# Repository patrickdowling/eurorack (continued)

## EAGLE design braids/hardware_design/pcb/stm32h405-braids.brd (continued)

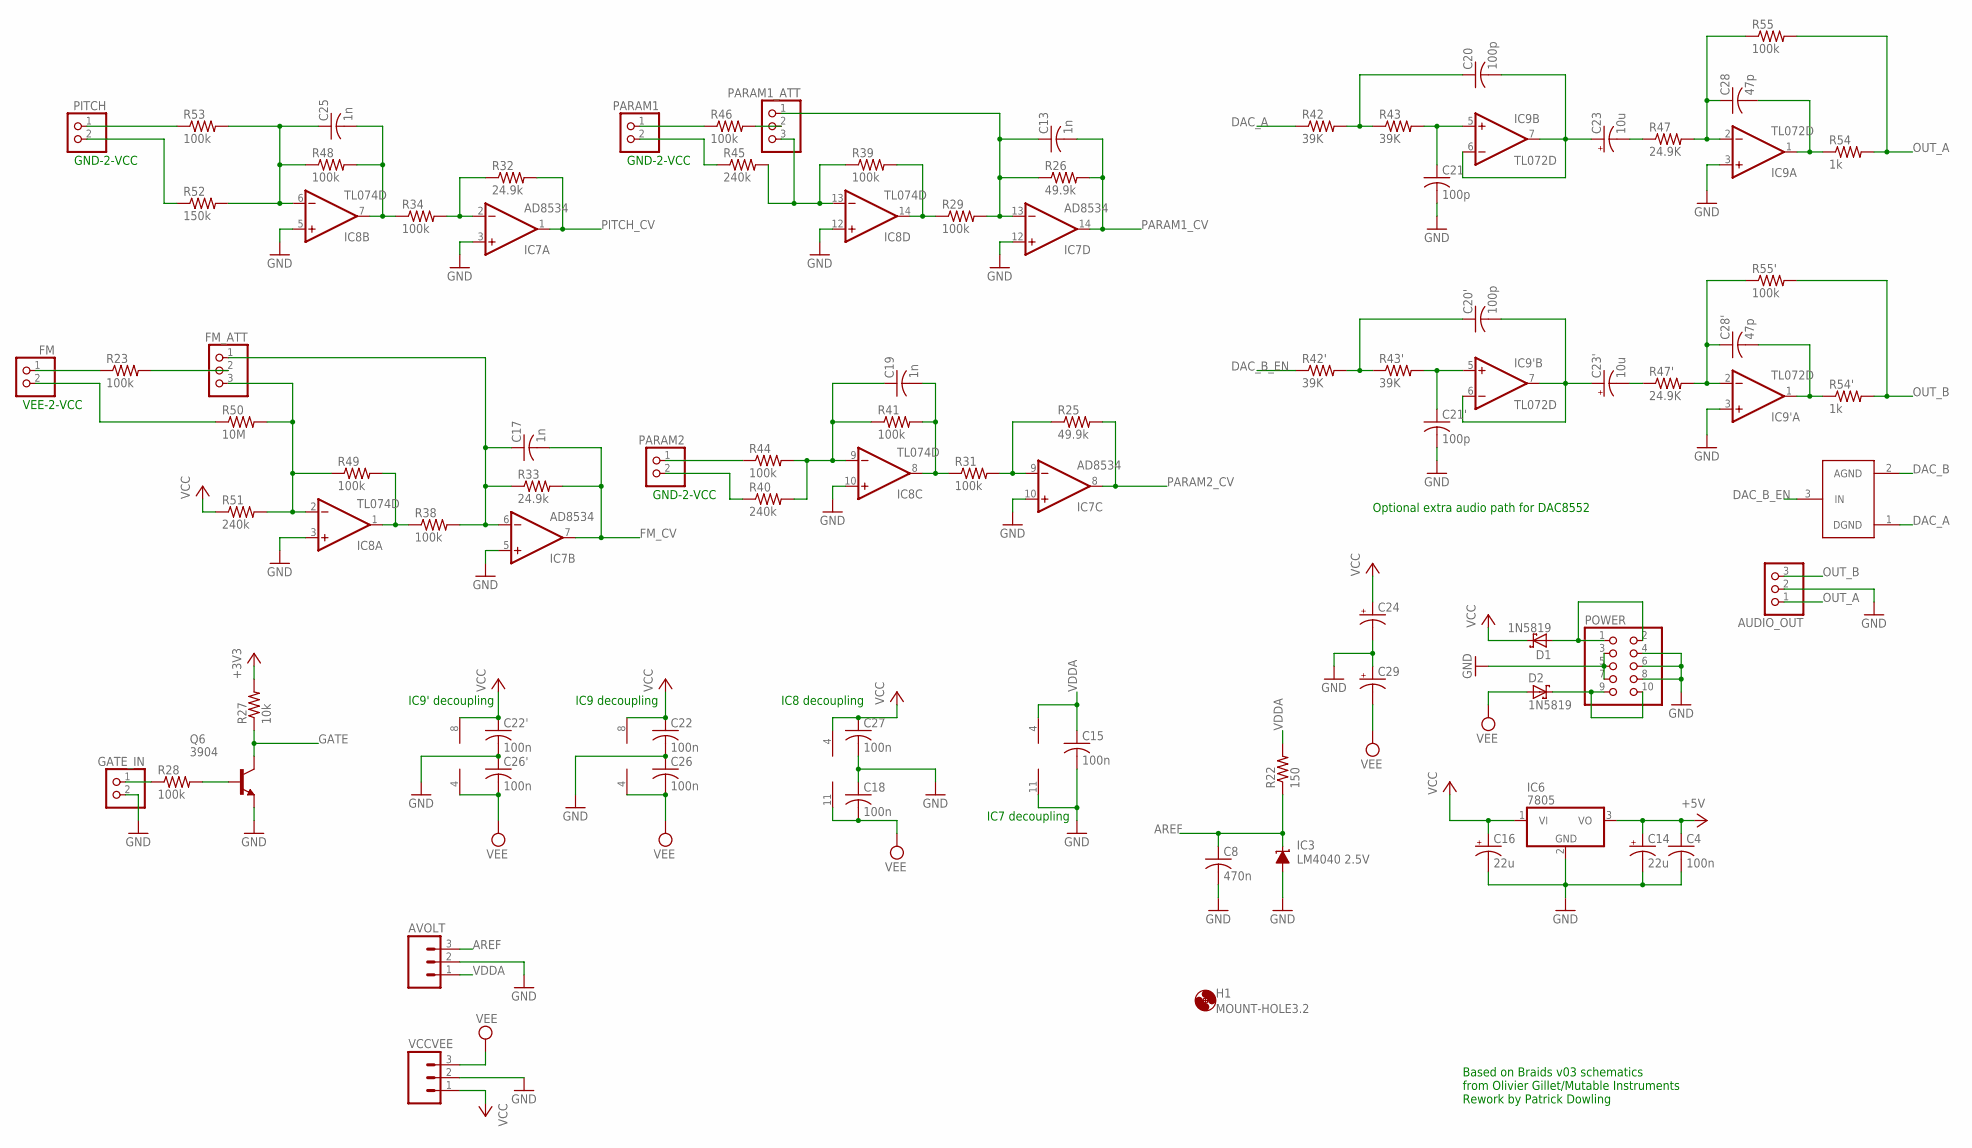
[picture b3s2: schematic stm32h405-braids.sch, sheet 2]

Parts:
AUDIO_OUT: PINHD-1X3; 1X03
AVOLT: M031X03_NO_SILK; 1X03_NO_SILK
C4: 100n; C025-024X044
C8: 470n; C0805
C13, C17, C19, C25: 1n; C0805
C14, C16: 22u; E2,5-6
C15, C18, C22, C22', C26, C26', C27: 100n; C0805
C20, C20', C21, C21': 100p; C0805
C23, C23': 10u; E2-5
C24, C29: CPOL-USE2.5-6; E2,5-6
C28, C28': 47p; C0805
D1, D2: 1N5819; DO41-7.6
DAC_CONF: GND_CONNECT
FM: PINHD-1X2; 1X02
FM_ATT: PINHD-1X3; 1X03
GATE_IN: PINHD-1X2; 1X02
H1: MOUNT-HOLE3.2; 3,2
IC3: LM4040 2.5V; DBZ_R-PDSO-G3
IC6: 7805; TO220V
IC7: AD8534; SO14
IC8: TL074D; SO14
IC9, IC9': TL072D; SO08
PARAM1, PARAM2: PINHD-1X2; 1X02
PARAM1_ATT: PINHD-1X3; 1X03
PITCH: PINHD-1X2; 1X02
POWER: PINHD-2X5; 2X05
Q6: 3904; SOT23-BEC
R22: 150; R0805
R23, R28, R29, R31, R34, R38, R39, R41, R44, R46, R48, R49, R53, R55, R55': 100k; R0805
R25, R26: 49.9k; R0805
R27: 10k; R0805
R32, R33: 24.9k; R0805
R40, R45, R51: 240k; R0805
R42, R42', R43, R43': 39K; R0805
R47, R47': 24.9K; R0805
R50: 10M; R0805
R52: 150k; R0805
R54, R54': 1k; R0805
VCCVEE: M031X03_NO_SILK; 1X03_NO_SILK

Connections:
+3V3: R27.2; also elsewhere on the board
+5V: C4.1, C14.+, IC6.3 (VO); also elsewhere on the board
AREF: AVOLT.3, C8.1, IC3.1 (C), R22.1; also elsewhere on the board
C28': C28'.2, IC9'.1 (OUT), R54'.1
DAC_A: DAC_CONF.1 (DGND), R42.1; also elsewhere on the board
DAC_B: DAC_CONF.2 (AGND); also elsewhere on the board
DAC_B_EN: DAC_CONF.3 (IN), R42'.1
FM_CV: C17.2, IC7.7 (OUT), R33.2; also elsewhere on the board
GATE: Q6.C, R27.1; also elsewhere on the board
GND: AUDIO_OUT.2, AVOLT.2, C4.2, C8.2, C14.-, C15.2, C16.-, C18.1, C21.2, C21'.2, C22.2, C22'.2, C24.-, C26.1, C26'.1, C27.2, C29.+, GATE_IN.2, IC3.2 (A), IC6.2 (GND), IC7.3 (+IN), IC7.5 (+IN), IC7.10 (+IN), IC7.11 (V-), IC7.12 (+IN), IC8.3 (+IN), IC8.5 (+IN), IC8.10 (+IN), IC8.12 (+IN), IC9.3 (+IN), IC9'.3 (+IN), POWER.3, POWER.4, POWER.5, POWER.6, POWER.7, POWER.8, Q6.E, VCCVEE.2; also elsewhere on the board
unnamed: D2.C, POWER.9, POWER.10
unnamed: D1.A, POWER.1, POWER.2
unnamed: C20.1, R42.2, R43.1
unnamed: C21.1, IC9.5 (+IN), R43.2
unnamed: C20.2, C23.+, IC9.6 (-IN), IC9.7 (OUT)
unnamed: C28.1, IC9.2 (-IN), R47.2, R55.1
unnamed: C23.-, R47.1
unnamed: C28.2, IC9.1 (OUT), R54.1
unnamed: FM_ATT.3, IC8.2 (-IN), R49.1, R50.2, R51.2
unnamed: IC8.1 (OUT), R38.1, R49.2
unnamed: FM.2, R50.1
unnamed: C25.2, IC8.7 (OUT), R34.1, R48.2
unnamed: C25.1, IC8.6 (-IN), R48.1, R52.2, R53.2
unnamed: IC8.14 (OUT), R29.1, R39.2
unnamed: IC8.13 (-IN), PARAM1_ATT.3, R39.1, R45.2
unnamed: C19.2, IC8.8 (OUT), R31.1, R41.2
unnamed: C19.1, IC8.9 (-IN), R40.2, R41.1, R44.2
unnamed: IC7.9 (-IN), R25.1, R31.2
unnamed: C17.1, FM_ATT.1, IC7.6 (-IN), R33.1, R38.2
unnamed: IC7.2 (-IN), R32.1, R34.2
unnamed: C13.1, IC7.13 (-IN), PARAM1_ATT.1, R26.1, R29.2
unnamed: Q6.B, R28.2
unnamed: FM_ATT.2, R23.2
unnamed: GATE_IN.1, R28.1
unnamed: FM.1, R23.1
unnamed: PITCH.1, R53.1
unnamed: PITCH.2, R52.1
unnamed: PARAM2.1, R44.1
unnamed: PARAM2.2, R40.1
unnamed: PARAM1.2, R45.1
unnamed: PARAM1.1, R46.1
unnamed: PARAM1_ATT.2, R46.2
unnamed: C20'.1, R42'.2, R43'.1
unnamed: C21'.1, IC9'.5 (+IN), R43'.2
unnamed: C20'.2, C23'.+, IC9'.6 (-IN), IC9'.7 (OUT)
unnamed: C28'.1, IC9'.2 (-IN), R47'.2, R55'.1
unnamed: C23'.-, R47'.1
OUT_A: AUDIO_OUT.1, R54.2, R55.2
OUT_B: AUDIO_OUT.3, R54'.2, R55'.2
PARAM1_CV: C13.2, IC7.14 (OUT), R26.2; also elsewhere on the board
PARAM2_CV: IC7.8 (OUT), R25.2; also elsewhere on the board
PITCH_CV: IC7.1 (OUT), R32.2; also elsewhere on the board
VCC: C16.+, C22.1, C22'.1, C24.+, C27.1, D1.C, IC6.1 (VI), IC8.4 (V+), IC9.8 (V+), IC9'.8 (V+), R51.1, VCCVEE.1
VDDA: AVOLT.1, C15.1, IC7.4 (V+), R22.2; also elsewhere on the board
VEE: C18.2, C26.2, C26'.2, C29.-, D2.A, IC8.11 (V-), IC9.4 (V-), IC9'.4 (V-), VCCVEE.3

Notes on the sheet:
IC8 decoupling
IC7 decoupling
IC9 decoupling
IC9' decoupling
GND-2-VCC
VEE-2-VCC
Based on Braids v03 schematics from Olivier Gillet/Mutable Instruments Rework by Patrick Dowling
Optional extra audio path for DAC8552

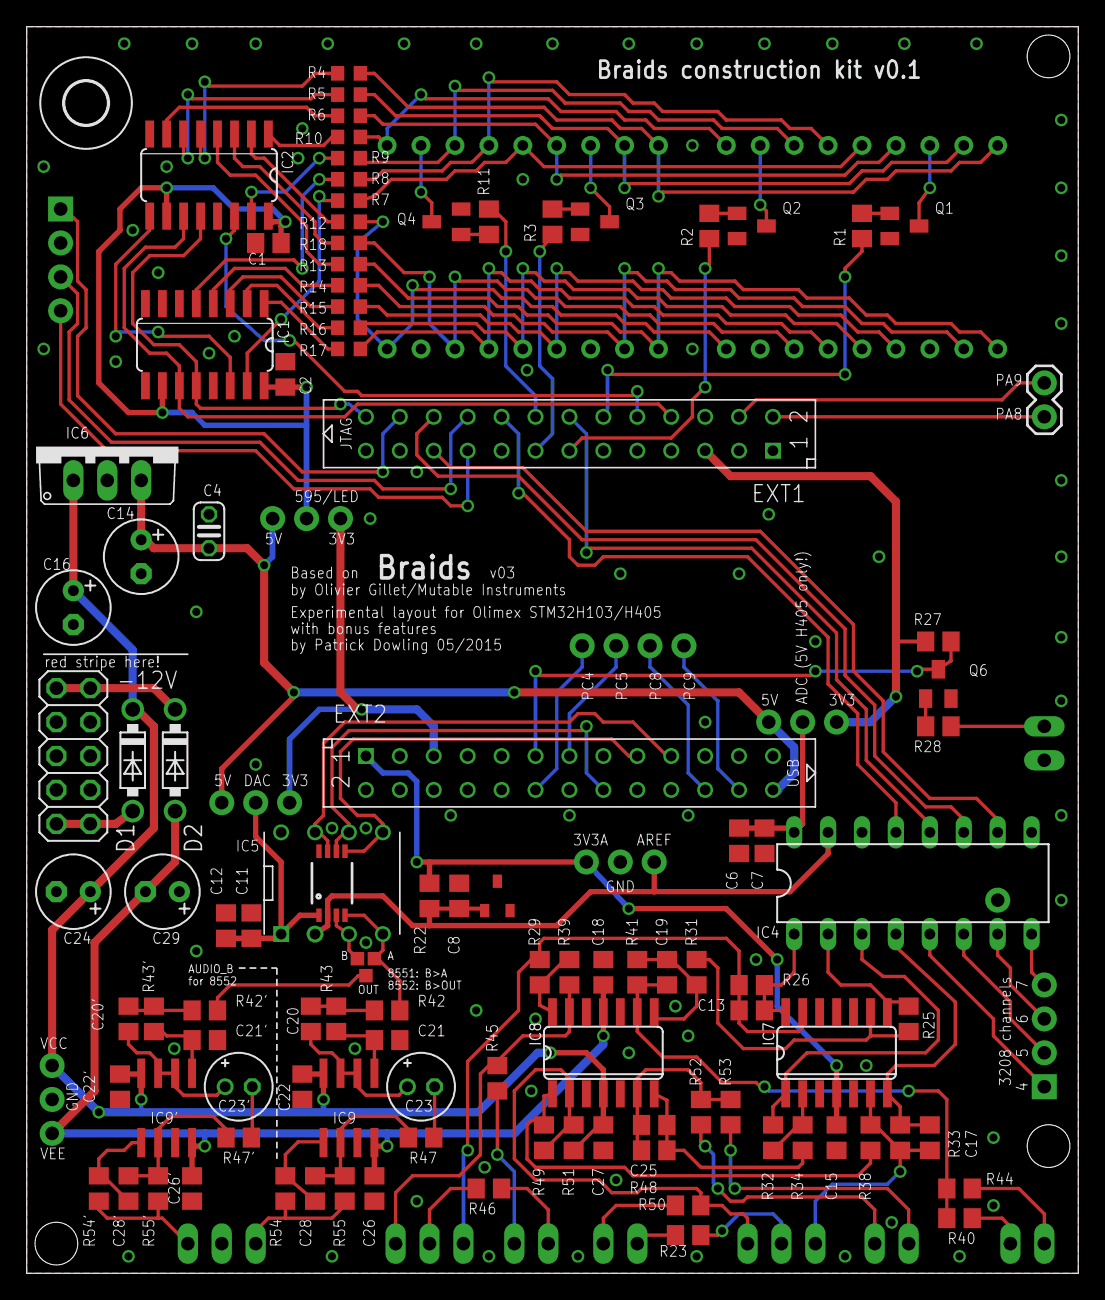
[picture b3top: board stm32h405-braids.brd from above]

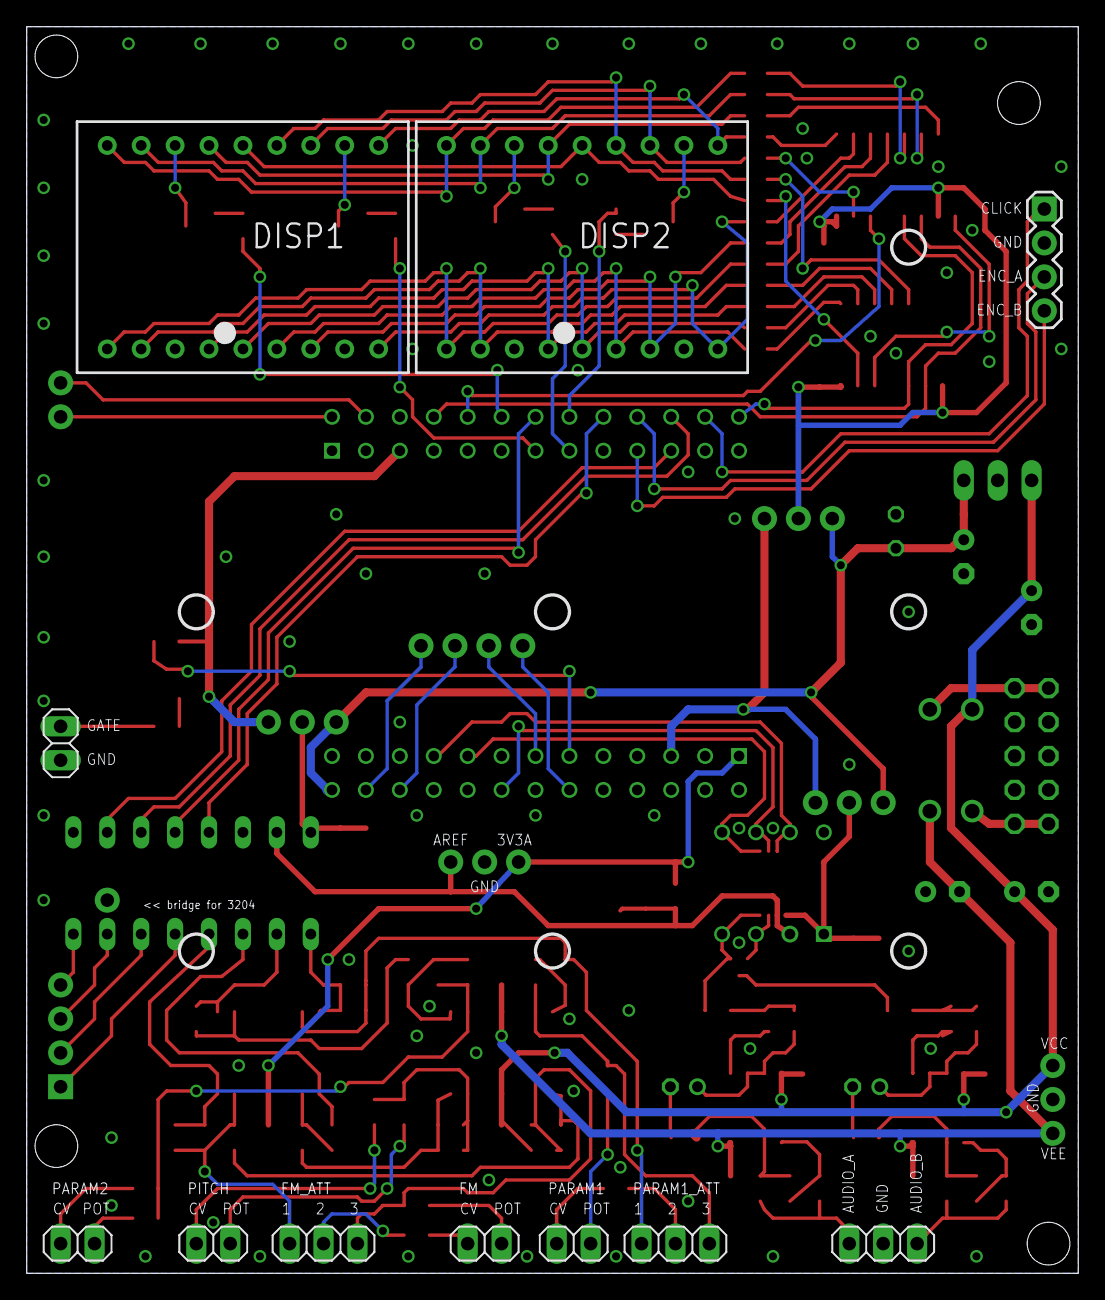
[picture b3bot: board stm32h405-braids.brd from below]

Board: 2 copper layers, 78.7 x 93.3 mm, 125 parts (11 on the bottom side), 123 nets.

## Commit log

2015-06-04 pcb/schematics for stm32h405/h103 based Braids
2015-06-06 Changed GPIOs for stm32h103/h405 pcb (untested). Use PROJECT_CONFIGURATION=-DOLIMEX_STM32 make to enable
2015-06-06 DISP_EN pin was also remapped (still untested)
2015-06-14 Start port to f405; main application compiles but is untested
2015-06-14 Makefile tweaks
2015-06-14 Bootstrap bootloader to get it compiling
2015-06-19 - Display works! - Find annoying typo in timer configuration, looks like it's working now too - Change makefile usage for simpler configuration of board type - Bootloader compiles but is bypassed but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
2015-06-20 Slight tweaks to DAC SPI, looks like it's working...
2015-06-20 Correct gpio initialization
2015-06-20 Experimental attempt to use DMA for DAC SPI (not working yet)
2015-06-28 Initial re-worked Braids PCB with H405 and simplified input section (work-in-progress)
2015-07-01 Add switches and LEDs, DAC uses +3V3_A
2015-07-04 Re-assign some GPIOs due to conflicts on Olimex boards, some tweaks
2015-07-05 Tweaks
2015-07-05 Yet another GPIO re-assign...
2015-07-06 Final tweaks
2015-07-08 0.2: Incorrectly placed audio jack
2015-08-15 Reworked GPIOs for Plaits prototype board, add UI stubs for switches
2015-08-15 Simple binary LED driver; PWM should be possible on those pins however.
2015-08-15 Bootstrap implementation for adc channels
2015-08-16 Fix dac gpio/spi assignments, enable GPIOD for debug pin
2015-08-16 Tweaks, looks like DAC output works
2015-08-16 Fix swapped display chars
2015-08-16 Activate internal ADC for all channels, extend CV meter to be able to show all available inputs
2015-08-16 Remove unnecessary distinction for f4/f1xx
2015-08-16 Test support for decimal points in display
2015-08-17 - Add skeleton code for CvScalar implementation - Temporary hack for DAC output which needs further investigation
2015-08-18 Additional debug menu to show raw ADC values
2015-08-18 Work in progress, mapping inputs/pots to "old" values
2015-08-19 Use left-aligned data and convert during cv scaling
2015-08-20 Experimental cv/pot reading with averaging
2015-08-21 Support trigger input (untested)
2015-08-21 Test implementation of attenuverter (probably should be scaled somehow)
2015-08-22 Simple LED/switch test
2015-08-23 Temporary fixes for nervous marquee that was using cv_ values and DAC timing issues
2015-08-23 Proof-Of-Concept attenuverter code, using all CV/pot inputs
2015-08-27 Board tweaks
2015-09-06 Closer to working pitch scaling, WIP calibration/settings
2015-09-07 Respect fm offset in CvScaler instead of converting range back and forth
2015-09-10 Fix magic byte check on load
2015-09-12 Use continuous ADC mode to oversample CV inputs x4 as a work-around for noisy inputs. ADC1 converts CV values, ADC2 pots (in non-continuous mode).
2015-09-12 Get DMA for SPI to DAC working. Leaving it enabled for now.
2015-09-13 Correct absolute pitch values (converted 16-12b at end of function)
2015-09-15 Manual trigger with switch, light led on trigger
2015-09-16 Disable pot lock in UI
2015-09-16 Rough implementation of alternate pot mapping, allows editing of AD settings without encoder.
2015-09-17 Try and make pot->setting mapping a bit more generic
2015-09-19 Clean up pot snapping/locking to make it clearer what's happening and hopefully fix lock/unlock/lock value change
2015-10-18 Convert to new ChunkStorage, so calibration data is stored separately to settings
2015-11-01 UI/panel mount PCB
2015-11-22 Remove original prototype pcb from this branch
2015-12-20 - Fix invalid defaults by initialising calibration/state before calling ChunkStorage::Init - Change tags in structs since ChunkStorage::RewriteSector was writing uninitialised values in first Init
2015-12-27 Disable CV control of marquee (fix pending), move mode indicator
2016-01-18 Tides: implement a quantizer - 7 selectable scales - select by long-pressing Mode button - calibration procedure access modified: press the Range button on startup. Cherry-picked from d12b434798ce93c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
2016-01-18 Tides: quantizer: remplace locrian by whole tones
2016-01-18 Tides: Ui: exit of quantizer mode via long-press on Mode. More practical than timeout. cherry-picked from 312438cb9c8c494cb73cc6f6c126df4606717330
2016-01-18 Tides: Ui: fix saving of quantizer setting cherry-picked from 0ee4f8f58e7d9c825db1840e169217bb02c67a79
2016-01-18 Tides: Ui: save state when switching quantization
2016-01-18 Tides: do not bypass VCA in quantizer and feature selection mode
2016-01-18 Tides: Quantizer: increase hysteresis and add filtering to pitch
    Avoids jitter between quantification steps.
2016-01-18 Tides: ui: add a magic number to make sure we load the right data Fixes a bug not saving the internal state when going back and forth between this firmware and the original one. cherry-picked from 7c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
2016-02-01 Tides: Change magic number
2016-02-01 Tides: Missing bit
2016-02-01 Tides: Apply IN_RAM to move IRQ handler and wavetable generator to RAM, this seems to fix some glitches
2016-07-11 [braids] Add ability to load saved state (i.e. normal startup state)
2016-07-11 [braids] Implement simple preset storage mechanism (no UI binding yet)
2016-07-11 [braids] UI for loading/saving presets, optionally preserving calibration data. Allows reset of state to defaults as well
2016-08-09 [braids] cosmetic
2016-11-13 [braids] Move preset storage pages to last 4k of bootloader flash area
2017-05-21 - Re-work calibration and v/oct scaling - CV inputs have calibrated 0V setting (since v/oct input might be configured differently)
